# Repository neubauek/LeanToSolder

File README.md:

# Omaha Do Space Lean to Solder Course Materials

Assembly instructions, presentation slides, and PCB design files.

Document and slides were created in Libre Office in case anyone has difficulty opening them.

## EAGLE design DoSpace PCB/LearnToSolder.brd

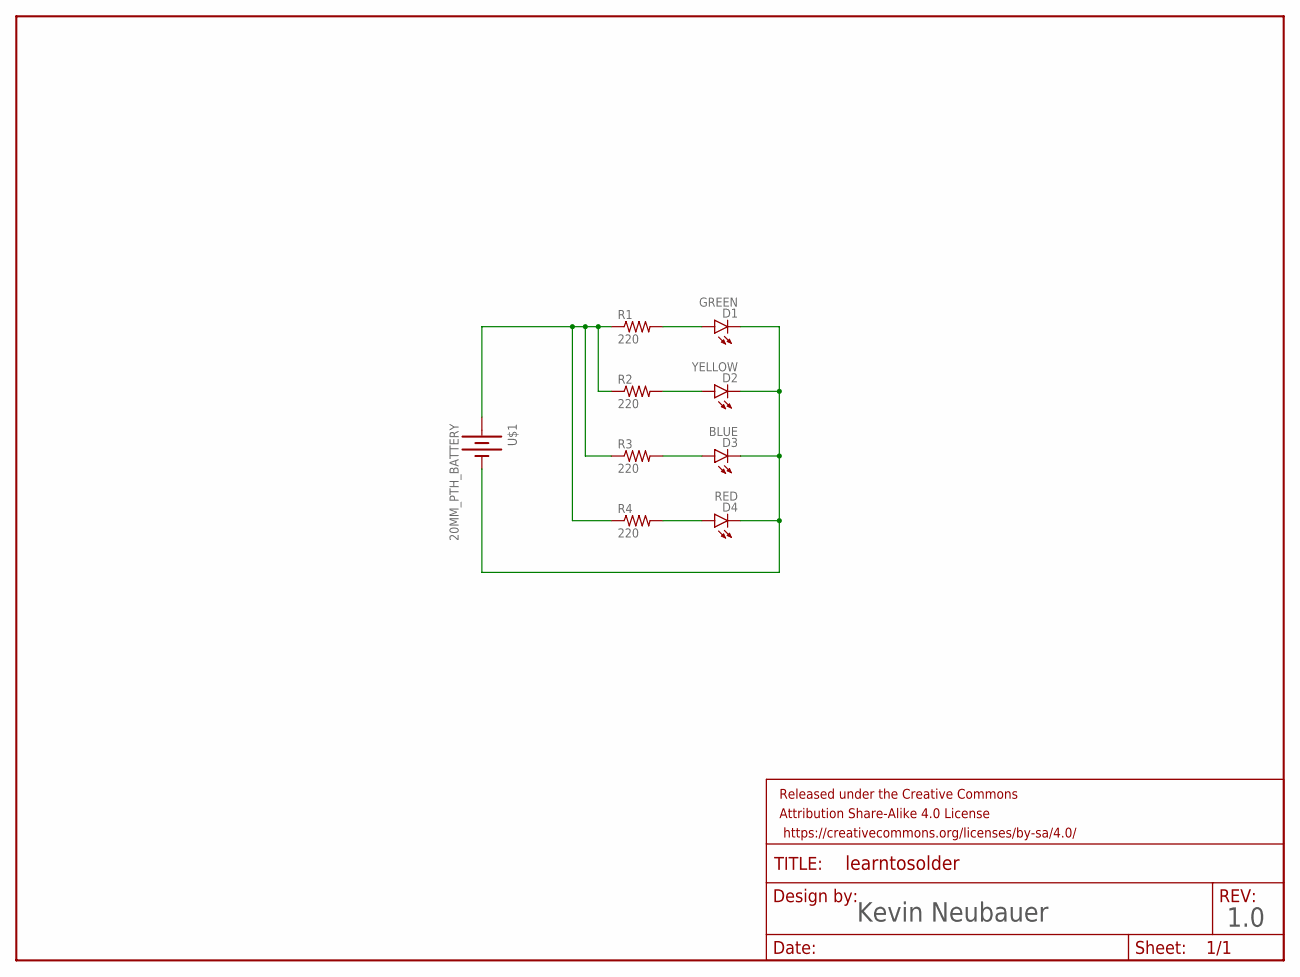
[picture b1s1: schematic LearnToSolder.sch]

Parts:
D1: GREEN; LED5MM
D2: YELLOW; LED5MM
D3: BLUE; LED5MM
D4: RED; LED5MM
FRAME1: FRAME-LETTER; CREATIVE_COMMONS
R1, R2, R3, R4: 220; AXIAL-0.4
U$1: 20MM_PTH_BATTERY; 20MM_PTH_CR2032

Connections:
3V3: R1.P$1 (1), R2.P$1 (1), R3.P$1 (1), R4.P$1 (1), U$1.1 (+), U$1.3 (+)
GND: D1.K (C), D2.K (C), D3.K (C), D4.K (C), U$1.2 (-)
unnamed: D1.A, R1.P$2 (2)
unnamed: D2.A, R2.P$2 (2)
unnamed: D3.A, R3.P$2 (2)
unnamed: D4.A, R4.P$2 (2)

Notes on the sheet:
Kevin Neubauer
1.0

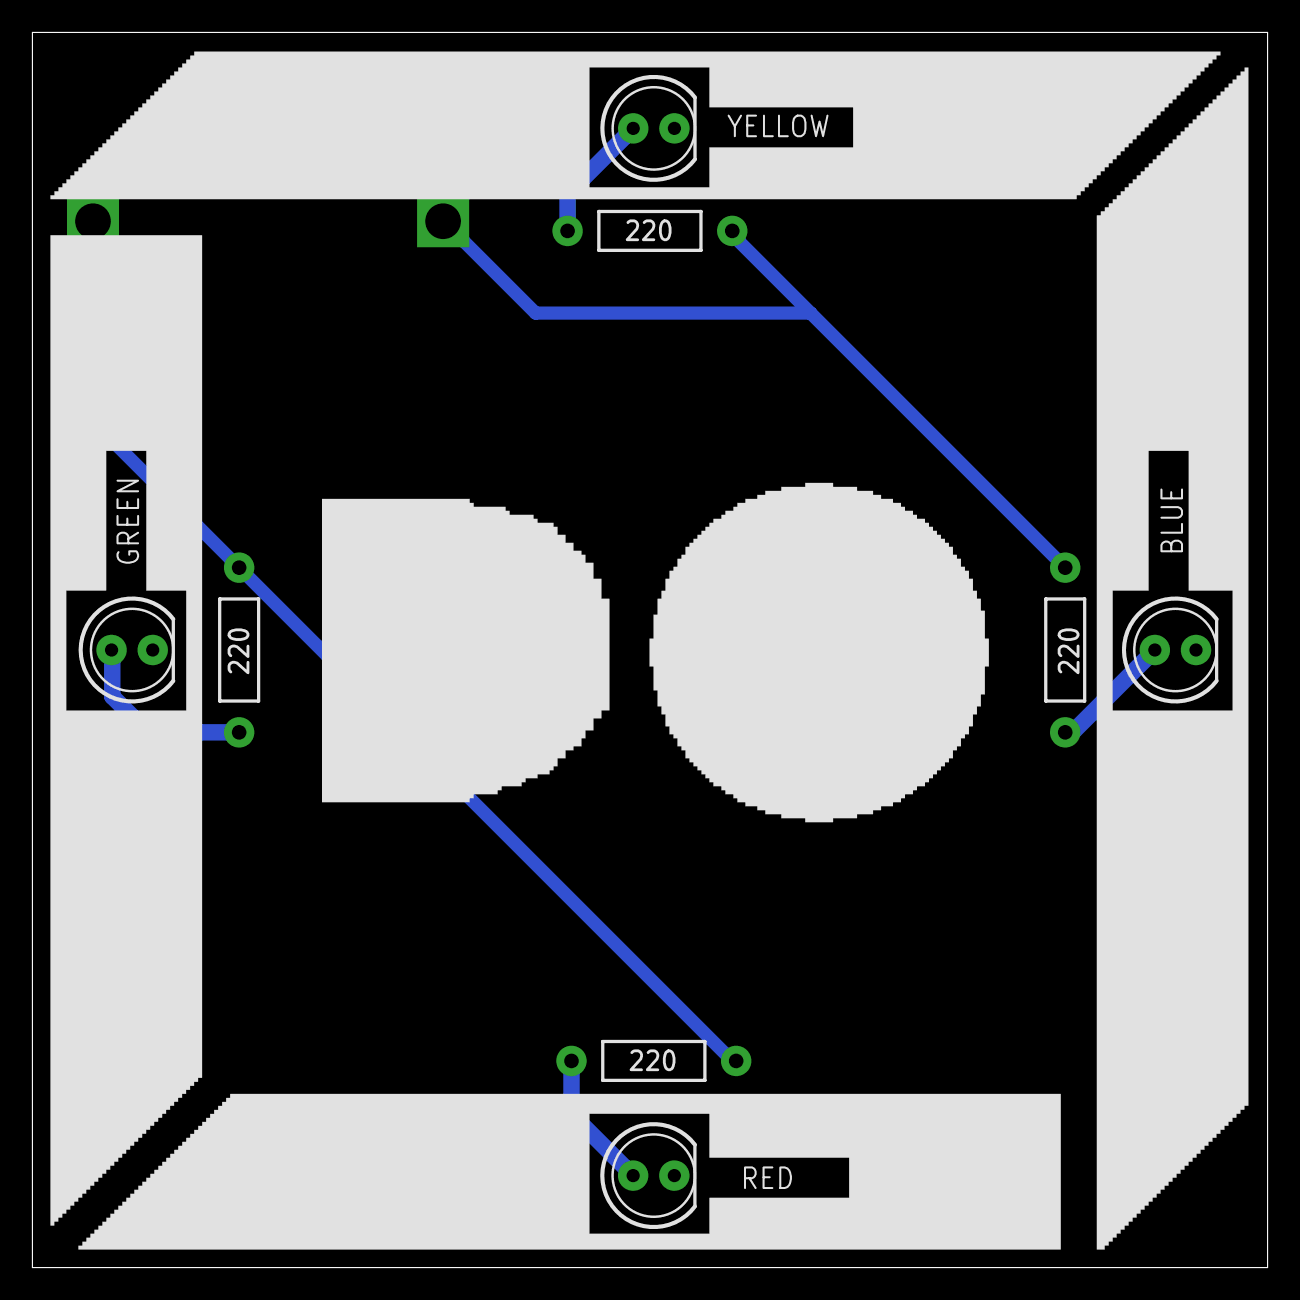
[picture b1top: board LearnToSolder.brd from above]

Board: 2 copper layers, 76.2 x 76.2 mm, 10 parts (1 on the bottom side), 6 nets.

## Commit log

2017-01-11 Initial Upload
2017-01-11 Added Readme
2017-01-11 Edited Readme
2017-01-12 Updated Slides
2017-01-12 Changed layout of slide 9
2017-04-27 Changes to Slides
    Some small changes to streamline slides

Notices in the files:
parts and their libraries:
SparkFun-Aesthetics: Licensing: Creative Commons ShareAlike 4.0 International - https://creativecommons.org/licenses/by-sa/4.0
SparkFun-Aesthetics: Released under the Creative Commons Attribution Share-Alike 4.0 License
SparkFun-Aesthetics: https://creativecommons.org/licenses/by-sa/4.0
